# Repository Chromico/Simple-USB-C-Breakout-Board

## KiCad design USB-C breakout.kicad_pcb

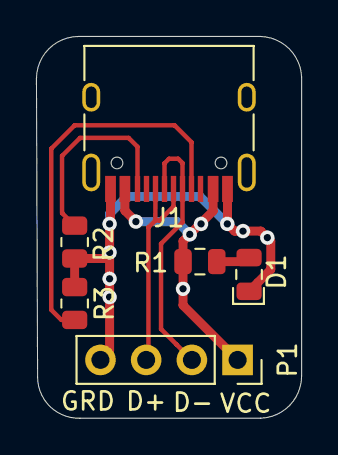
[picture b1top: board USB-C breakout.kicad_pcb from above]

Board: 2 copper layers, 14.7 x 21.2 mm, 6 parts (0 on the bottom side), 7 nets.

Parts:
D1: LED; C_0805_2012Metric
J1: USB_C_Receptacle_USB2.0; USB_C_Receptacle_HRO_TYPE-C-31-M-12
P1: Conn_01x04_MountingPin; PinSocket_1x04_P2.54mm_Vertical
R1: 1K; C_0805_2012Metric
R2, R3: 5.11K; R_0805_2012Metric

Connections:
/D+: J1.A6 (D+), J1.B6 (D+), P1.3
/D-: J1.A7 (D-), J1.B7 (D-), P1.2
/VCC: J1.A4 (VBUS), J1.A9 (VBUS), J1.B4 (VBUS), J1.B9 (VBUS), P1.1, R1.2
GND: D1.1 (K), J1.A1 (GND), J1.A12 (GND), J1.B1 (GND), J1.B12 (GND), P1.4, R2.1, R3.1
unnamed: D1.2 (A), R1.1
unnamed: J1.A5 (CC1), R3.2
unnamed: J1.B5 (CC2), R2.2

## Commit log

2022-02-19 Add CC resistors
2022-02-19 Create LICENSE
